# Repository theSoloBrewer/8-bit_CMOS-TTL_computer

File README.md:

# 8-bit_CMOS-TTL_computer
8 Bit CMOS/TTL computer inspired by Ben Eater and DrMattRegan on YouTube

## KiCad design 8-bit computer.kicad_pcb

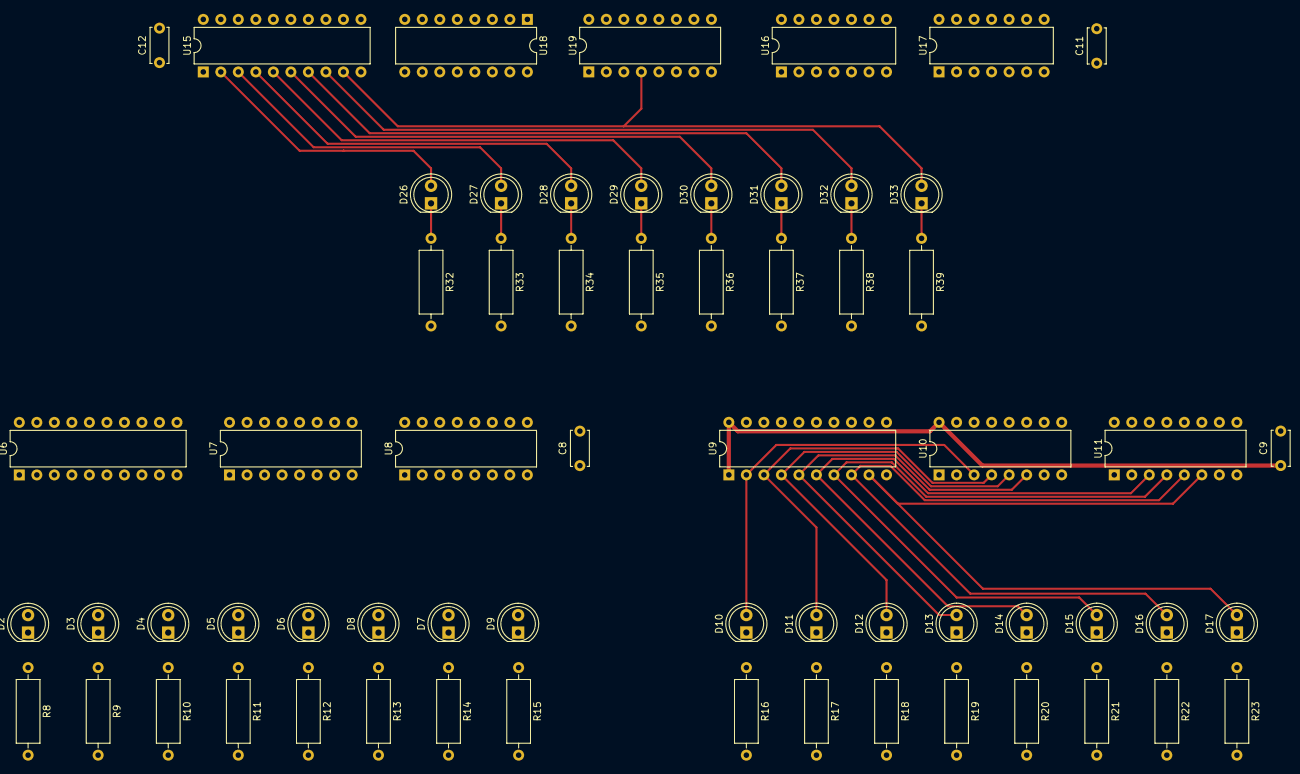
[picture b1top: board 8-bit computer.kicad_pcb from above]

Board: 2 copper layers, 63 parts (0 on the bottom side), 69 nets.

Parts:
C8, C9, C11, C12: 0.1uF; C_Disc_D5.0mm_W2.5mm_P5.00mm
D2, D3, D4, D5, D6, D7, D8, D9, D10, D11, D12, D13, D14, D15, D16, D17, D26, D27, D28, D29, D30, D31, D32, D33: LED; LED_D5.0mm
R8, R9, R10, R11, R12, R13, R14, R15, R16, R17, R18, R19, R20, R21, R22, R23, R32, R33, R34, R35, R36, R37, R38, R39: 1K; R_Axial_DIN0309_L9.0mm_D3.2mm_P12.70mm_Horizontal
U6, U9, U15: 74HC245; DIP-20_W7.62mm
U7, U8, U10, U11: 74HC173; DIP-16_W7.62mm
U16, U17: 74LS86; DIP-14_W7.62mm
U18, U19: 74LS283; DIP-16_W7.62mm

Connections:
/ALU/A_0: D2.2 (A), U6.2 (A0), U7.3 (Q0), U19.5 (A1)
/ALU/A_1: D3.2 (A), U6.3 (A1), U7.4 (Q1), U19.3 (A2)
/ALU/A_2: D4.2 (A), U6.4 (A2), U7.5 (Q2), U19.14 (A3)
/ALU/A_3: D5.2 (A), U6.5 (A3), U7.6 (Q3), U19.12 (A4)
/ALU/A_4: D6.2 (A), U6.6 (A4), U8.3 (Q0), U18.5 (A1)
/ALU/A_5: D7.2 (A), U6.7 (A5), U8.4 (Q1), U18.3 (A2)
/ALU/A_6: D8.2 (A), U6.8 (A6), U8.5 (Q2), U18.14 (A3)
/ALU/A_7: D9.2 (A), U6.9 (A7), U8.6 (Q3), U18.12 (A4)
/ALU/B_0: D10.2 (A), U9.2 (A0), U10.3 (Q0), U17.12
/ALU/B_1: D11.2 (A), U9.3 (A1), U10.4 (Q1), U17.9
/ALU/B_2: D12.2 (A), U9.4 (A2), U10.5 (Q2), U17.4
/ALU/B_3: D13.2 (A), U9.5 (A3), U10.6 (Q3), U17.1
/ALU/B_4: D14.2 (A), U9.6 (A4), U11.3 (Q0), U16.12
/ALU/B_5: D15.2 (A), U9.7 (A5), U11.4 (Q1), U16.9
/ALU/B_6: D16.2 (A), U9.8 (A6), U11.5 (Q2), U16.4
/ALU/B_7: D17.2 (A), U9.9 (A7), U11.6 (Q3), U16.1
/ALU/Data_Bus0: U6.18 (B0), U8.11 (D3), U9.18 (B0), U11.11 (D3), U15.11 (B7)
/ALU/Data_Bus1: U6.17 (B1), U8.12 (D2), U9.17 (B1), U11.12 (D2), U15.12 (B6)
/ALU/Data_Bus2: U6.16 (B2), U8.13 (D1), U9.16 (B2), U11.13 (D1), U15.13 (B5)
/ALU/Data_Bus3: U6.15 (B3), U8.14 (D0), U9.15 (B3), U11.14 (D0), U15.14 (B4)
/ALU/SU: U16.2, U16.5, U16.10, U16.13, U17.2, U17.5, U17.10, U17.13, U19.7 (C0)
/ALU/SUM0: D26.2 (A), U15.2 (A0), U18.10 (S4)
/ALU/SUM1: D27.2 (A), U15.3 (A1), U18.13 (S3)
/ALU/SUM2: D28.2 (A), U15.4 (A2), U18.1 (S2)
/ALU/SUM3: D29.2 (A), U15.5 (A3), U18.4 (S1)
/ALU/SUM4: D30.2 (A), U15.6 (A4), U19.10 (S4)
/ALU/SUM5: D31.2 (A), U15.7 (A5), U19.13 (S3)
/ALU/SUM6: D32.2 (A), U15.8 (A6), U19.1 (S2)
/ALU/SUM7: D33.2 (A), U15.9 (A7), U19.4 (S1)
/ALU/s_0: U17.11, U19.6 (B1)
/ALU/s_1: U17.8, U19.2 (B2)
/ALU/s_2: U17.6, U19.15 (B3)
/ALU/s_3: U17.3, U19.11 (B4)
/ALU/s_4: U16.11, U18.6 (B1)
/ALU/s_5: U16.8, U18.2 (B2)
/ALU/s_6: U16.6, U18.15 (B3)
/ALU/s_7: U16.3, U18.11 (B4)
/Clock Module/~CLK: U7.7 (Cp), U8.7 (Cp), U10.7 (Cp), U11.7 (Cp)
/Register A/CLR: U7.15 (Mr), U8.15 (Mr)
/Register A/~RI: U7.9 (E1), U7.10 (E2), U8.9 (E1), U8.10 (E2)
/Register B/CLR: U10.15 (Mr), U11.15 (Mr)
/Register B/~RI: U10.9 (E1), U10.10 (E2), U11.9 (E1), U11.10 (E2)
GND: C8.2, C9.2, C11.1, C12.2, R8.2, R9.2, R10.2, R11.2, R12.2, R13.2, R14.2, R15.2, R16.2, R17.2, R18.2, R19.2, R20.2, R21.2, R22.2, R23.2, R32.2, R33.2, R34.2, R35.2, R36.2, R37.2, R38.2, R39.2, U6.10 (GND), U6.11 (B7), U6.12 (B6), U6.13 (B5), U6.14 (B4), U7.1 (Oe1), U7.2 (Oe2), U7.8 (GND), U7.11 (D3), U7.12 (D2), U7.13 (D1), U7.14 (D0), U8.1 (Oe1), U8.2 (Oe2), U8.8 (GND), U9.10 (GND), U9.11 (B7), U9.12 (B6), U9.13 (B5), U9.14 (B4), U10.1 (Oe1), U10.2 (Oe2), U10.8 (GND), U10.11 (D3), U10.12 (D2), U10.13 (D1), U10.14 (D0), U11.1 (Oe1), U11.2 (Oe2), U11.8 (GND), U15.15 (B3), U15.16 (B2), U15.17 (B1), U15.18 (B0), U16.7 (GND), U17.7 (GND), U18.8 (GND), U19.8 (GND)
unnamed: D2.1 (K), R8.1
unnamed: D3.1 (K), R9.1
unnamed: D4.1 (K), R10.1
unnamed: D5.1 (K), R11.1
unnamed: D6.1 (K), R12.1
unnamed: D7.1 (K), R13.1
unnamed: D8.1 (K), R14.1
unnamed: D9.1 (K), R15.1
unnamed: D10.1 (K), R16.1
unnamed: D11.1 (K), R17.1
unnamed: D12.1 (K), R18.1
unnamed: D13.1 (K), R19.1
unnamed: D14.1 (K), R20.1
unnamed: D15.1 (K), R21.1
unnamed: D16.1 (K), R22.1
unnamed: D17.1 (K), R23.1
unnamed: D26.1 (K), R32.1
unnamed: D27.1 (K), R33.1
unnamed: D28.1 (K), R34.1
unnamed: D29.1 (K), R35.1
unnamed: D30.1 (K), R36.1
unnamed: D31.1 (K), R37.1
unnamed: D32.1 (K), R38.1
unnamed: D33.1 (K), R39.1
unnamed: U18.7 (C0), U19.9 (C4)
VCC: C8.1, C9.1, C11.2, C12.1, U6.1 (A->B), U6.20 (VCC), U7.16 (VCC), U9.1 (A->B), U9.20 (VCC), U10.16 (VCC), U15.1 (A->B), U16.14 (VCC), U17.14 (VCC), U18.16 (VCC), U19.16 (VCC)

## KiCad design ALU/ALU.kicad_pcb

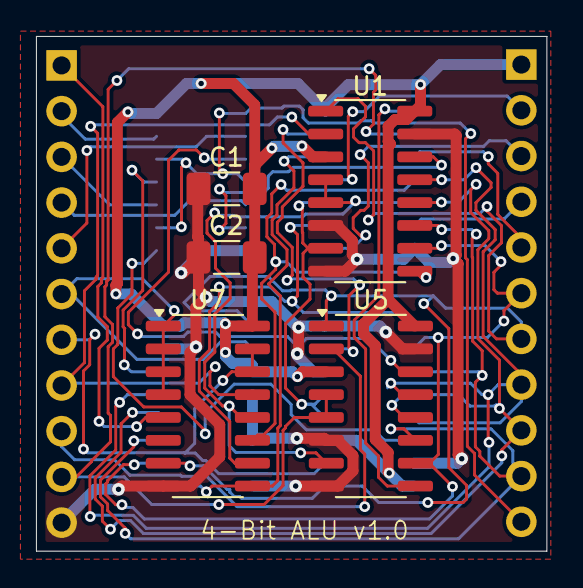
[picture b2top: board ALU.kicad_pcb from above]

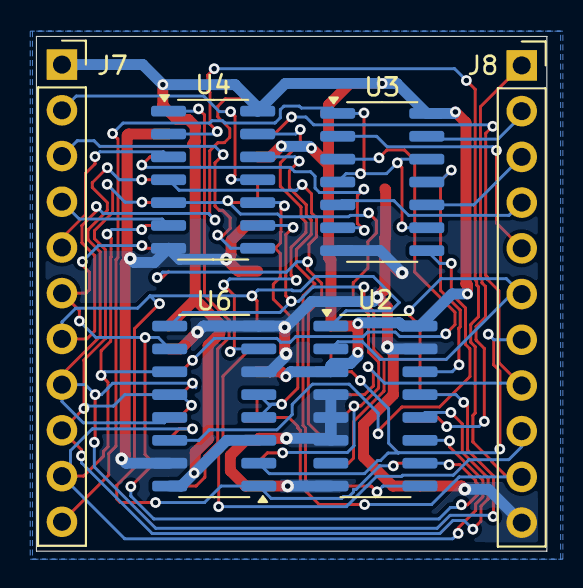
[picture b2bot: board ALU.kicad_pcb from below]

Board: 2 copper layers, 28.4 x 28.6 mm, 11 parts (6 on the bottom side), 33 nets.

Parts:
C1, C2: 100nF; C_1206_3216Metric_Pad1.33x1.80mm_HandSolder
J7: Conn_01x11_Socket; PinSocket_1x11_P2.54mm_Vertical
J8: Conn_01x10_Socket; PinSocket_1x11_P2.54mm_Vertical
U1, U2, U5, U6: 74HC153; SOIC-16_3.9x9.9mm_P1.27mm
U3, U4: 74LS86; SOIC-14_3.9x8.7mm_P1.27mm
U7: 74LS151; SOIC-16_3.9x9.9mm_P1.27mm

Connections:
/4-bit2/A0: J8.5, U3.2
/4-bit2/A1: J8.4, U3.5
/4-bit2/A2: J8.3, U3.10
/4-bit2/A3: J8.2, U3.13
/4-bit2/B0: J8.9, U5.2 (S1)
/4-bit2/B1: J8.8, U1.2 (S1), U7.13 (I6)
/4-bit2/B2: J8.7, U6.2 (S1), U7.14 (I5), U7.15 (I4)
/4-bit2/B3: J8.6, U2.2 (S1), U7.1 (I3), U7.2 (I2), U7.3 (I1), U7.4 (I0)
/4-bit2/C0: U1.4 (I2a), U1.5 (I1a), U4.5, U5.7 (Za), U7.12 (I7)
/4-bit2/C1: U1.7 (Za), U4.10, U6.4 (I2a), U6.5 (I1a)
/4-bit2/C2: U4.13, U6.7 (Za)
/4-bit2/Cin: J8.10, U4.2, U5.4 (I2a), U5.5 (I1a)
/4-bit2/Cout: J8.1, U7.5 (Z)
/4-bit2/F0: J7.11, U3.1, U3.4, U3.9, U3.12
/4-bit2/F1: J7.10, U1.11 (I1b), U2.11 (I1b), U5.11 (I1b), U6.11 (I1b)
/4-bit2/F2: J7.9, U1.12 (I2b), U2.12 (I2b), U5.12 (I2b), U6.12 (I2b)
/4-bit2/F3: J7.8, U1.13 (I3b), U2.13 (I3b), U5.13 (I3b), U6.13 (I3b)
/4-bit2/F4: J7.7, U1.1 (Ea), U2.1 (Ea), U5.1 (Ea), U6.1 (Ea), U7.7 (~E)
/4-bit2/F5: J7.6, U1.10 (I0b), U2.10 (I0b), U5.10 (I0b), U6.10 (I0b)
/4-bit2/OUT0: J7.5, U4.3
/4-bit2/OUT1: J7.4, U4.6
/4-bit2/OUT2: J7.3, U4.8
/4-bit2/OUT3: J7.2, U4.11
/4-bit2/P0: U4.1, U5.9 (Zb)
/4-bit2/P1: U1.9 (Zb), U4.4, U7.11 (S0)
/4-bit2/P2: U4.9, U6.9 (Zb), U7.10 (S1)
/4-bit2/P3: U2.9 (Zb), U4.12, U7.9 (S2)
GND: C1.2, C2.2, J8.11, U1.6 (I0a), U1.8 (GND), U1.15 (Eb), U2.4 (I2a), U2.5 (I1a), U2.6 (I0a), U2.8 (GND), U2.15 (Eb), U3.7 (GND), U4.7 (GND), U5.6 (I0a), U5.8 (GND), U5.15 (Eb), U6.6 (I0a), U6.8 (GND), U6.15 (Eb), U7.8 (GND)
unnamed: U1.14 (S0), U3.6
unnamed: U2.14 (S0), U3.11
unnamed: U3.3, U5.14 (S0)
unnamed: U3.8, U6.14 (S0)
VCC: C1.1, C2.1, J7.1, U1.3 (I3a), U1.16 (VCC), U2.3 (I3a), U2.16 (VCC), U3.14 (VCC), U4.14 (VCC), U5.3 (I3a), U5.16 (VCC), U6.3 (I3a), U6.16 (VCC), U7.16 (VCC)

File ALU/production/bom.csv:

Designator,Footprint,Quantity,Value,LCSC Part #
"C1, C2",1206,2,100nF,
"U1, U2, U5, U6",SOIC-16_3.9x9.9mm_P1.27mm,4,74HC153,
"U3, U4",SOIC-14_3.9x8.7mm_P1.27mm,2,74LS86,
U7,SOIC-16_3.9x9.9mm_P1.27mm,1,74LS151,

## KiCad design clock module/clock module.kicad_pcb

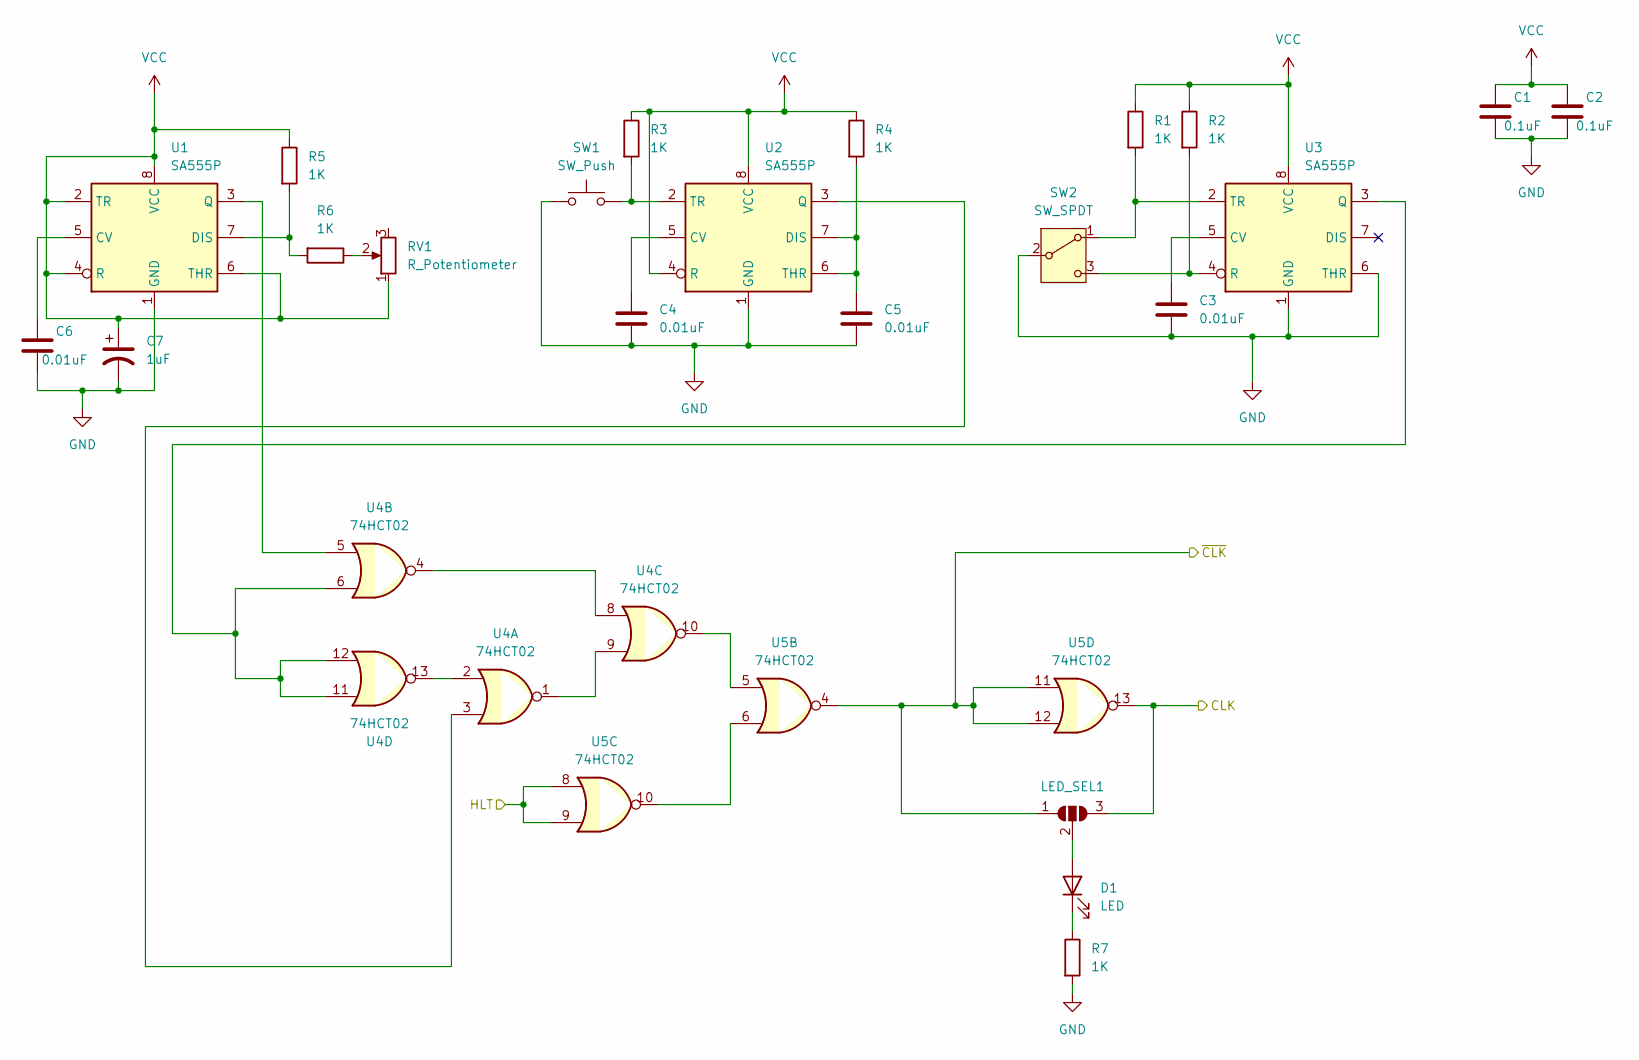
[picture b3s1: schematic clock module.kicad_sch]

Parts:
C1, C2: 0.1uF; C_Disc_D5.0mm_W2.5mm_P5.00mm
C3, C4, C5, C6: 0.01uF; C_Disc_D5.0mm_W2.5mm_P5.00mm
C7: 1uF; CP_Radial_D5.0mm_P2.00mm
D1: LED; LED_D5.0mm
LED_SEL1: SolderJumper_3_Open; SolderJumper-3_P1.3mm_Open_RoundedPad1.0x1.5mm
R1, R2, R3, R4, R5, R6, R7: 1K; R_Axial_DIN0309_L9.0mm_D3.2mm_P12.70mm_Horizontal
RV1: R_Potentiometer; Potentiometer_Bourns_PTV09A-1_Single_Vertical
SW1: SW_Push; SW_PUSH_6mm_H4.3mm
SW2: SW_SPDT; SW_Push_2P2T_Toggle_CK_PVA2OAH5xxxxxxV2
U1, U2, U3: SA555P; DIP-8_W7.62mm
U4, U5: 74HCT02; DIP-14_W7.62mm

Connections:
/CLK: LED_SEL1.3 (B), U5.13; also elsewhere on the board
/HLT: U5.8, U5.9; also elsewhere on the board
/~CLK: LED_SEL1.1 (A), U5.4, U5.11, U5.12; also elsewhere on the board
GND: C1.1, C2.2, C3.2, C4.2, C5.2, C6.2, C7.2, R7.2, SW1.1, SW2.2 (B), U1.1 (GND), U2.1 (GND), U3.1 (GND), U3.6 (THR), U4.7 (GND), U5.7 (GND); also elsewhere on the board
LED_SEL: D1.2 (A), LED_SEL1.2 (C); also elsewhere on the board
unnamed: D1.1 (K), R7.1
unnamed: R6.1, RV1.2
unnamed: R1.2, SW2.1 (A), U3.2 (TR)
unnamed: R2.2, SW2.3 (C), U3.4 (R)
unnamed: C6.1, U1.5 (CV)
unnamed: R5.2, R6.2, U1.7 (DIS)
unnamed: U1.3 (Q), U4.5
unnamed: C4.1, U2.5 (CV)
unnamed: C5.1, R4.2, U2.6 (THR), U2.7 (DIS)
unnamed: U2.3 (Q), U4.3
unnamed: R3.2, SW1.2, U2.2 (TR)
unnamed: C3.1, U3.5 (CV)
unnamed: U3.3 (Q), U4.6, U4.11, U4.12
unnamed: U4.1, U4.9
unnamed: U4.4, U4.8
unnamed: U4.10, U5.5
unnamed: U4.2, U4.13
unnamed: U5.6, U5.10
VCC: C1.2, C2.1, C7.1, R1.1, R2.1, R3.1, R4.1, R5.1, RV1.1, U1.2 (TR), U1.4 (R), U1.6 (THR), U1.8 (VCC), U2.4 (R), U2.8 (VCC), U3.8 (VCC), U4.14 (VCC), U5.14 (VCC); also elsewhere on the board

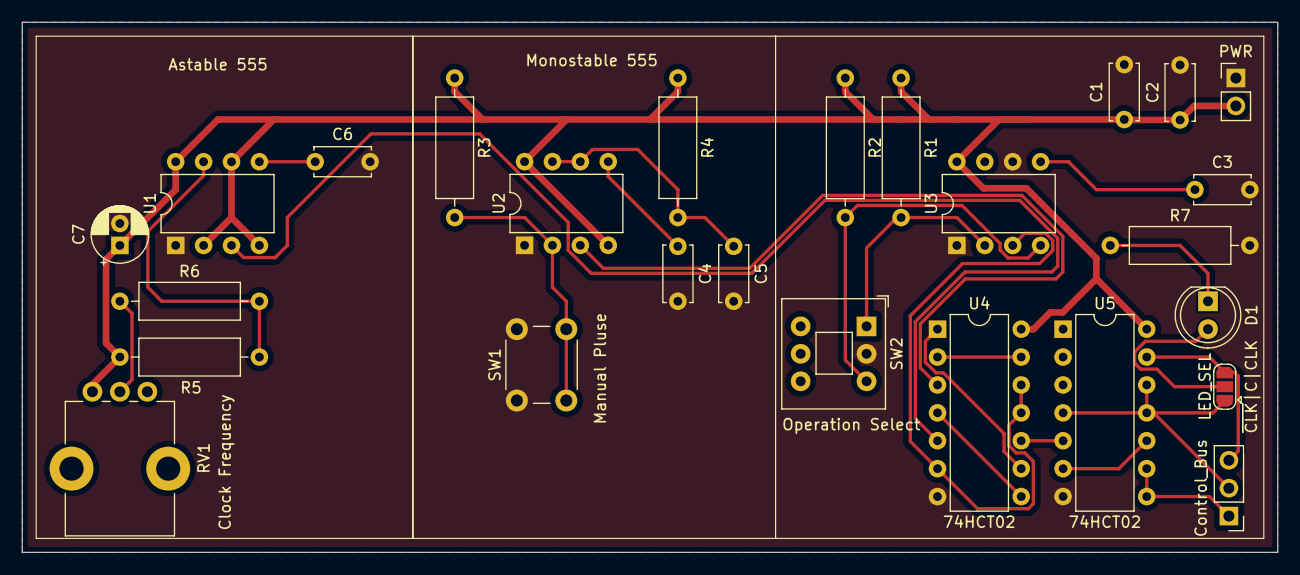
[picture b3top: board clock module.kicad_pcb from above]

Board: 2 copper layers, 114.3 x 48.3 mm, 26 parts (0 on the bottom side), 24 nets.

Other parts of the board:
Control_Bus: PinHeader_1x03_P2.54mm_Vertical
LED_SEL: ~{CLK}|C|CLK; SolderJumper-3_P1.3mm_Open_RoundedPad1.0x1.5mm
PWR: PinHeader_1x02_P2.54mm_Vertical

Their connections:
/CLK: Control_Bus.3, LED_SEL.3; also elsewhere on the board
/HLT: Control_Bus.1; also elsewhere on the board
/~CLK: Control_Bus.2, LED_SEL.1; also elsewhere on the board
GND: PWR.1; also elsewhere on the board
LED_SEL: LED_SEL.2; also elsewhere on the board
VCC: PWR.2; also elsewhere on the board

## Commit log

2024-10-22 Upload work on new ALU
2024-10-22 Create Flag/Status Register
2024-10-22 Expanding the block diagram
2024-10-22 update to ignore file
